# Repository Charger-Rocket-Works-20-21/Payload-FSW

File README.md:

# Payload-FSW
Payload flight software for the 2021 USLI Competition Team from the University of Alabama in Huntsville

Uses:
* a Teensy 4.1 (with Teensyduino add-on)
* a Bosch BMP386
* a Bosch BNO055
* a NTCLE thermistor
* a Xbee Radio, and
* 

Dependencies:
* Arduino Libraries (Wire, SPI)
* Adafruit BNO055 Library
* Adafruit BMP3XX Library

Tasks:
* Query Positional Sensor
* Query Pressure Sensor
* Query Temperature Sensor
* Calculate Altitude from Pressure and Temperature
* Detect Landing
* Level Payload
* Take Pictures of Landed Surroundings
* Transmit Telemetry and Photographed Surroundings

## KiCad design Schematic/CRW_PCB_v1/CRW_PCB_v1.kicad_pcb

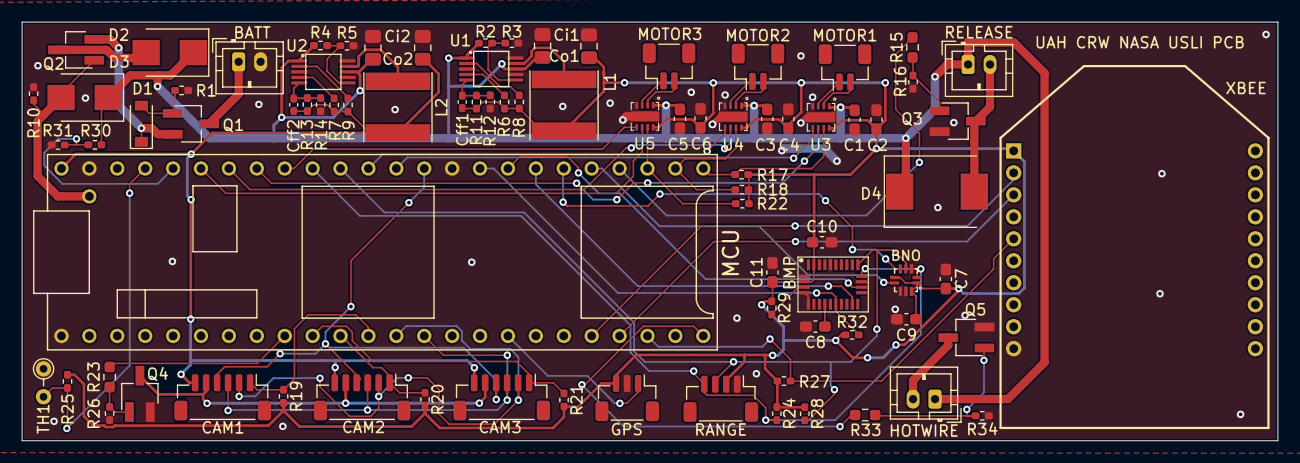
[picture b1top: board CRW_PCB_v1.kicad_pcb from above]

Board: 2 copper layers, 114.3 x 38.1 mm, 83 parts (0 on the bottom side), 64 nets.

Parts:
BATT: BATTERIES; JST_PH_B2B-PH-K_1x02_P2.00mm_Vertical
BMP: BNO055; LGA28R50P4X10_380X520X100
BNO: BMP388; PQFN50P200X200X80-10N
C1, C2, C3, C4, C5, C6, C7, C9, C11: 0.1uF; C_0603_1608Metric_Pad1.08x0.95mm_HandSolder
C8: 1uF; C_0603_1608Metric_Pad1.08x0.95mm_HandSolder
C10: 120nF; C_0603_1608Metric_Pad1.08x0.95mm_HandSolder
CAM1, CAM2, CAM3: CAMERA; JST_SH_BM06B-SRSS-TB_1x06-1MP_P1.00mm_Vertical
Cff1, Cff2: 6.8pF; C_0402_1005Metric_Pad0.74x0.62mm_HandSolder
Ci1, Ci2: 10uF; C_0805_2012Metric_Pad1.18x1.45mm_HandSolder
Co1, Co2: 22uF; C_0805_2012Metric_Pad1.18x1.45mm_HandSolder
D1: D_Zener; D_SOD-123
D2, D3: D_Schottky; D_SMB
D4: FLYBACK; D_SMC
GPS: GPS_Connector; JST_SH_BM03B-SRSS-TB_1x03-1MP_P1.00mm_Vertical
HOTWIRE: HOTWIRE; JST_PH_B2B-PH-K_1x02_P2.00mm_Vertical
L1, L2: 10uH; L_Taiyo-Yuden_NR-60xx
MCU: TEENSY 4.1; DEV-16771
MOTOR1: LEVEL1; JST_SH_BM02B-SRSS-TB_1x02-1MP_P1.00mm_Vertical
MOTOR2: LEVEL2; JST_SH_BM02B-SRSS-TB_1x02-1MP_P1.00mm_Vertical
MOTOR3: LEVEL3; JST_SH_BM02B-SRSS-TB_1x02-1MP_P1.00mm_Vertical
Q1, Q2: Q_PMOS_GSD; SC-59_Handsoldering
Q3, Q4, Q5: Q_NMOS_GSD; SC-59_Handsoldering
R1, R10, R16, R17, R18, R22, R26, R27, R29, R32, R34: 10k; R_0402_1005Metric_Pad0.72x0.64mm_HandSolder
R2, R4: 130k; R_0402_1005Metric_Pad0.72x0.64mm_HandSolder
R3, R5, R12, R30: 100k; R_0402_1005Metric_Pad0.72x0.64mm_HandSolder
R6, R7, R8, R9: 1M; R_0402_1005Metric_Pad0.72x0.64mm_HandSolder
R11: 560k; R_0402_1005Metric_Pad0.72x0.64mm_HandSolder
R13: 820k; R_0402_1005Metric_Pad0.72x0.64mm_HandSolder
R14: 91k; R_0402_1005Metric_Pad0.72x0.64mm_HandSolder
R15, R23, R33: 220; R_0603_1608Metric_Pad0.98x0.95mm_HandSolder
R19, R20, R21, R24, R28: 4.7k; R_0402_1005Metric_Pad0.72x0.64mm_HandSolder
R25, R31: 47k; R_0402_1005Metric_Pad0.72x0.64mm_HandSolder
RANGE: QWIIC_Connector; JST_SH_BM04B-SRSS-TB_1x04-1MP_P1.00mm_Vertical
RELEASE: AUTOGYRO_RELEASE; JST_PH_B2B-PH-K_1x02_P2.00mm_Vertical
TH1: Thermistor; R_Axial_DIN0204_L3.6mm_D1.6mm_P2.54mm_Vertical
U1, U2: TPS62051DGS; TPS62051DGS_VSSOP
U3, U4, U5: DRV8838DSGR
XBEE: XBEE Wire; DIP2200W51P200L3294H279Q20P

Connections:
+3V3: BMP.3, BMP.28, BNO.1, BNO.6, BNO.10, C2.1, C4.1, C6.1, C7.2, C9.1, C10.1, C11.1, Cff1.1, Co1.1, GPS.3, L1.2, R6.1, R8.1, R11.1, R17.2, R18.2, R19.2, R20.2, R21.2, R22.2, R24.1, R25.1, R27.1, R28.1, R29.1, R32.1, RANGE.2, U3.8, U4.8, U5.8, XBEE.1
+5V: CAM1.6, CAM2.6, CAM3.6, Cff2.1, Co2.1, L2.2, MCU.VIN, R7.1, R9.1, R13.1
+BATT: C1.1, C3.1, C5.1, Ci1.1, Ci2.1, D2.1, D3.1, D4.1, HOTWIRE.1, R2.1, R4.1, R30.1, RELEASE.1, U1.1, U1.8, U2.1, U2.8, U3.1, U4.1, U5.1
-BATT: BATT.2, BMP.2, BMP.5, BMP.6, BMP.18, BMP.25, BNO.3, BNO.8, BNO.9, C1.2, C2.2, C3.2, C4.2, C5.2, C6.2, C7.1, C8.2, C9.2, C10.2, C11.2, Ci1.2, Ci2.2, Co1.2, Co2.2, GPS.2, MCU.AGND, MCU.GND, MCU.GND@1, Q3.2, Q4.2, Q5.2, R1.1, R3.2, R5.2, R10.2, R12.2, R14.2, R16.2, R26.2, R31.2, R34.2, RANGE.1, TH1.1, U1.3, U1.7, U1.10, U2.3, U2.7, U2.10, U3.4, U3.9, U4.4, U4.9, U5.4, U5.9, XBEE.10
BATT_ADC: MCU.D22/A8, R30.2, R31.1
BMP_ADDR_SEL: BNO.5, MCU.D38/A14
BMP_INT: BNO.7, MCU.D37
CAM1_SS: CAM1.1, MCU.D10, R19.1
CAM2_SS: CAM2.1, MCU.D9, R20.1
CAM3_SS: CAM3.1, MCU.D8, R21.1
CAM_PWR: MCU.D7, R23.2
GPS_UART_MISO: GPS.1, MCU.D25/A11
GYRO_RELEASE: MCU.D36, R15.2
HOTWIRE: MCU.D32, R33.2
I2C_SCL: BMP.19, BNO.2, MCU.D17/A3, R24.2, RANGE.4
I2C_SDA: BMP.20, BNO.4, MCU.D16/A2, R28.2, RANGE.3
IMU_ADDR_SEL: BMP.17, MCU.D40/A16
IMU_INT: BMP.14, MCU.D39/A15
IMU_~RESET: BMP.11, MCU.D41/A17, R32.2
LEVEL1_DIR: MCU.D19/A5, U3.6
LEVEL1_PWM: MCU.D14/A0, U3.5
LEVEL1_~SLEEP: MCU.D33, R17.1, U3.7
LEVEL2_DIR: MCU.D20/A6, U4.6
LEVEL2_PWM: MCU.D15/A1, U4.5
LEVEL2_~SLEEP: MCU.D34, R18.1, U4.7
LEVEL3_DIR: MCU.D21/A7, U5.6
LEVEL3_PWM: MCU.D18/A4, U5.5
LEVEL3_~SLEEP: MCU.D35, R22.1, U5.7
unnamed: BATT.1, Q1.3
unnamed: BMP.4, R29.2
unnamed: BMP.9, C8.1
unnamed: CAM1.5, CAM2.5, CAM3.5, Q4.3
unnamed: Cff1.2, R11.2, R12.1, U1.5
unnamed: Cff2.2, R13.2, R14.1, U2.5
unnamed: D1.1, Q1.2, Q2.2
unnamed: D1.2, Q1.1, R1.2
unnamed: D2.2, Q2.3
unnamed: D4.2, Q3.3, RELEASE.2
unnamed: HOTWIRE.2, Q5.3
unnamed: L1.1, U1.9
unnamed: L2.1, U2.9
unnamed: MOTOR1.1, U3.3
unnamed: MOTOR1.2, U3.2
unnamed: MOTOR2.1, U4.3
unnamed: MOTOR2.2, U4.2
unnamed: MOTOR3.1, U5.3
unnamed: MOTOR3.2, U5.2
unnamed: Q3.1, R15.1, R16.1
unnamed: Q4.1, R23.1, R26.1
unnamed: Q5.1, R33.1, R34.1
unnamed: R2.2, R3.1, U1.6
unnamed: R4.2, R5.1, U2.6
unnamed: R6.2, U1.4
unnamed: R7.2, U2.4
unnamed: R8.2, U1.2
unnamed: R9.2, U2.2
SPI_MISO: CAM1.3, CAM2.3, CAM3.3, MCU.D12
SPI_MOSI: CAM1.2, CAM2.2, CAM3.2, MCU.D11
SPI_SCLK: CAM1.4, CAM2.4, CAM3.4, MCU.D13/LED
THERM_ADC: MCU.D23/A9, R25.2, TH1.2
USB_PWR: D3.2, MCU.VUSB, Q2.1, R10.1
XBEE_UART_MISO: MCU.D28, XBEE.2
XBEE_UART_MOSI: MCU.D29, XBEE.3
XBEE_~RESET: MCU.D30, R27.2, XBEE.5

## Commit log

2020-11-02 Created Framework
2020-11-02 Added IMU and Altimeter test code
2020-11-03 Made Some updates
2020-11-03 Made Initialization Non-Specific
2020-11-03 File management and ring bufers
2020-11-03 More Formatting
2020-11-03 Restructured to make more sense with system.h
2020-11-05 Added urls to reference pages
2020-11-06 moved to header source folder
2020-11-06 Move files into folders
2020-11-06 Working on setting up PlatformIO
2020-11-06 Think this should work
2020-11-12 Added clock frequency build parameter
2020-11-12 Tested PIO on Teensy LC
2020-11-12 Commented out clock parameter
2020-11-18 Added Flight State Logic and fleshed out Main
2020-11-18 Added Sensor Readings
2020-11-20 Added drivers for SD Card Writing
2020-12-15 Began Schematic and Added Flight Logic for Drop Tests
2020-12-16 Drop test changes
2020-12-19 KiCAD work
2020-12-20 Functional Drop Test Code
2020-12-21 Schematic work
2020-12-22 More Schematic Work
2020-12-24 Finished Schematic
2020-12-25 Removed .lib from .gitignore
2020-12-27 Maybe Finished PCB
2020-12-28 Finished PCB v1
2020-12-28 Change Power connectors
2020-12-28 Used Hierarchical Sheets
2021-01-18 Added XBee, untested
2021-01-20 Added Hotwire Connection
2021-01-25 Xbee Work for Drop Test/Ground Station
2021-01-28 Added Thermistor Drivers
2021-02-06 Finished Drop Test
2021-02-06 Drop Test Release Code
2021-02-15 Serial Studio JSON work
2021-02-22 Added rangefinder drivers
2021-02-23 Create ReadMe.txt
    test
2021-02-25 Added PID drivers, needs slight rework on some aspects
2021-02-27 Reworked main to be more like the working droptest project
2021-03-01 Added Level Test
2021-03-01 Finished Detach Mechanism
2021-03-02 Intermediate Commit
    Thinking about way to structure serial manager. Right now it's a process, but doing it with signals/slots will probably work better.
2021-03-03 Serial Communication
    Created serial device manager. Works enough to connect to another instance of itself and send data back and forth. Needs more signals/slots to change settings on the port though.
2021-03-04 Basic Serial Stuff Implemented
    Can send/receive multiple messages. Created really basic process which will simulate and send flight data to the ground station.
2021-03-04 Level Test Updates
2021-03-05 Working Detach Test
2021-03-05 Fingers crossed leveler works
2021-03-05 Added support for images
    Program can now interpret images and save them. It can also interpret the other telemetry, but it doesn't do anything with it yet.
2021-03-05 Connected telemetryProcessed Signal to CSV Writer
    Program now writes all received telemetry to csv file
2021-03-05 Broke everything except sending images
    Images send like a million times faster if they're sent directly as the bytes of the image, so I did that, which messed up all the other stuff temporarily.
2021-03-06 Mostly works with LEDs and hand leveling, should work better with motors
2021-03-09 Threaded Serial Reading
    Threaded all of the Serial stuff and wrapped it in a manager. This prevents the ui/graphing stuff from interrupting the Serial Reading or trying to write a variable twice. (This would cause major err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
2021-03-17 Untested Main
2021-03-18 Camera Updates
2021-03-19 Appears to mostly work
2021-03-19 Massive Changes, reverting to DropTest and building up
2021-03-19 Added in Flight States and Softwire framework
2021-03-19 Updated final version
2021-03-19 Works on Uno with BNO055
2021-03-20 Added relevant settings for Serial
    Added port selection and baud rate selection to UI
2021-03-23 Probably all works but the cameras
2021-03-24 Tweaks to final and leveling in attempts to troubleshoot
2021-03-24 Integrated functioning camera code into Final (not tested)
2021-03-25 Added fixed poll rate, transmission rate, and reset through EEPROM
2021-03-25 Tweaked flight states
2021-03-26 Added camera commands and sending logic
2021-03-26 Tweaks attempting to get XBee commands working
2021-03-26 Final Ground Station Update
2021-03-27 Added zip file to upload .exe file
2021-03-27 Fixing Build Issues
2021-03-31 Works for everything but cameras
2021-04-01 Transfer to desktop
2021-04-01 Working Camera Codegit add .!
2021-04-02 Small updates
2021-04-03 Sometimes working leveling
2021-04-04 Added quaternion logic
2021-04-05 It worked once
2021-04-05 Can now go up to +/- 180 degrees heading
2021-04-06 It worked TWICE now
2021-04-06 Leveling Works, unless the payload rotates over 180 degrees
2021-04-06 Fixed 180 overload bug
2021-04-06 Integrated Leveling into Main
2021-04-07 Fixed File naming problems, but now cameras don't work
2021-04-08 Small groundstation changes
    Added button to clear plots under window options on toolbar. Some other small things. Did not rebuild exe.
2021-04-09 Pls don't blue screen
2021-04-09 Camera transmission tweaks
2021-04-10 Drop Test Tweaks
2021-04-11 VS Code Workspace
2021-04-13 Transmission Tweaks for Nathan
2021-04-14 Transmission working on this commit
    Don't remember exactly what I did, something with the 0 byte and removing a comma and some println, but it works.
2021-04-14 Should fill in correct image when requested
2021-04-22 Working Cameras
2021-04-22 GroundStation Compiled OPEN MEEEE
2021-04-24 Final Changes
2021-04-25 Hopefully made panorama stuff work even with one camera
2021-04-25 Added executable
